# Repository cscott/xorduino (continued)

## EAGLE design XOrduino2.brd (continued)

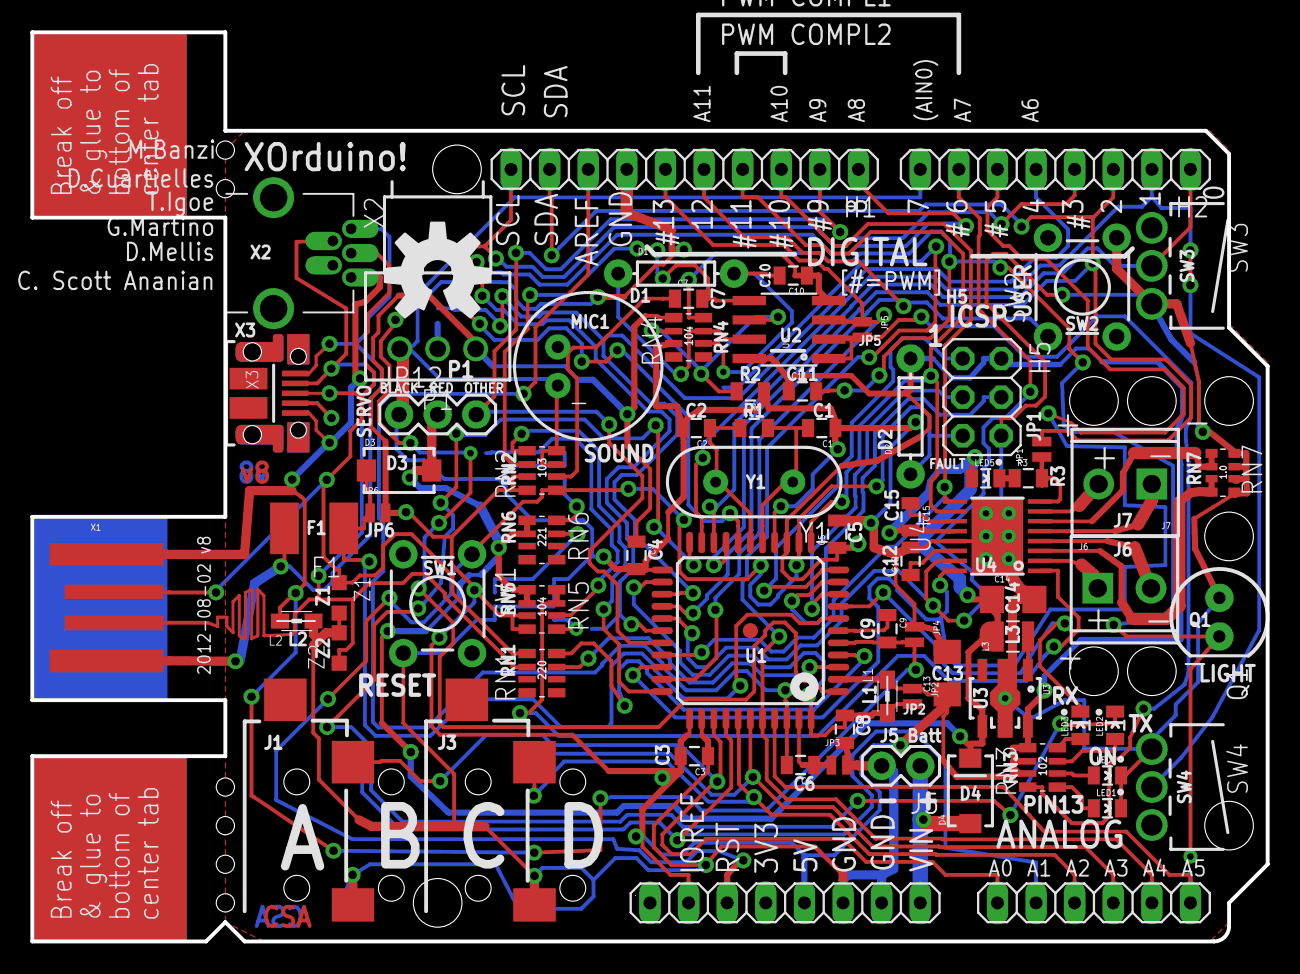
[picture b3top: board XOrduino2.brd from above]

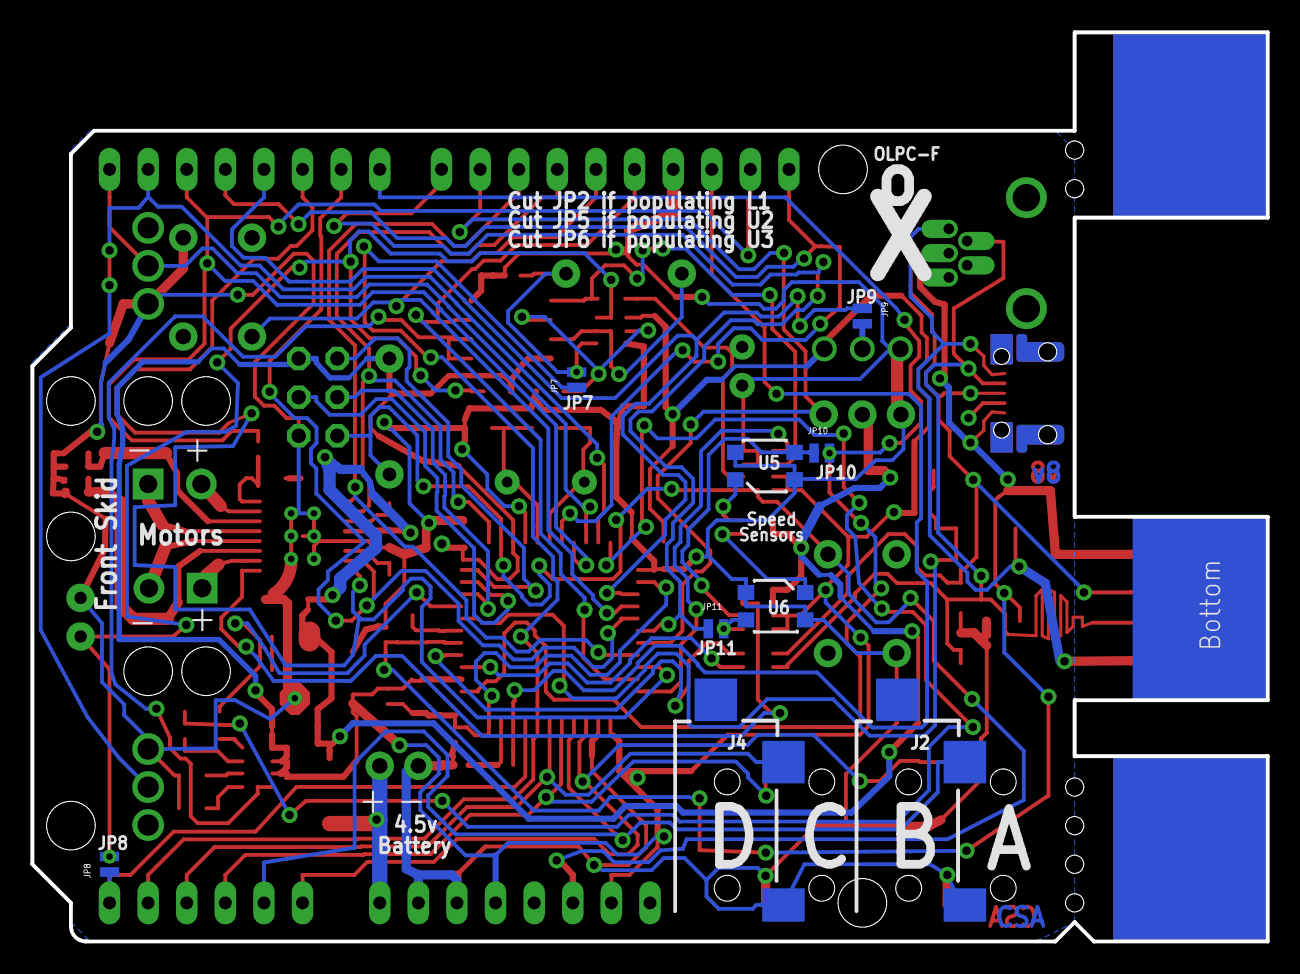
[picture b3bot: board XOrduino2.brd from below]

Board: 4 copper layers, 81.3 x 59.8 mm, 82 parts (4 on the bottom side), 72 nets.

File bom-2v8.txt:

Here's my suggested XO Stick and XOrduino BOMs, with just the bits
really necessary (not all the extras).

The XOrduino BOM was put together with Mitch Bradley's help.  Thanks!

Here is the XOrduino DigiKey BOM organized by sections.  You can paste
individual sections directly into the "Create New BOM (Text File
Import)" dialog.

-- Basic
2,311-1102-1-ND,C1 C2 - 18pF 0805
4,311-1361-1-ND,C2 C3 C4 C5 C6 - 100nF 0805
1,ATMEGA32U4-AU-ND,U1 - ATMEGA32U4-AU
1,445-1589-1-ND,C9 - 1uF
1,587-1356-1-ND,C13 22uF 1206
1,507-1363-1-ND,F1 - 6V 1.1A 1812 PTC Resettable Fuse
1,754-1135-1-ND,LED1 - LED yellow 0805
2,475-1415-1-ND,LED2 LED3 - LED red 0805
1,475-1410-1-ND,LED4 - LED green 0805
10,CRA6S822CT-ND,RN1 - 4x22R (1 required, minimum order is 10)
10,CRA6S810KCT-ND,RN2 - 4x10K (1 required, minimum order is 10)
10,CRA6S81.0KCT-ND,RN3 - 4x1K (1 required, minimum order is 10)
1,450-1652-ND,SW1 - tactile switch
1,CTX1085-ND,Y1 - 16MHz 18pF crystal
1,609-3550-ND,H1 - 10-pin female
2,609-3559-ND,H2 H3 - 8-pin female
1,609-3558-ND,H4 - 6-pin female
1,609-3218-ND,H5 - 3-pin 2-row header

-- Optional
1,311-1.0MARCT-ND,R1 - 1M 0805
1,1N4148FS-ND,D1 - 1N4148
1,445-1589-1-ND,C8 - 1uF 0805
2,L1 L2 - ferrite bead 30 ohm
1,WM17115-ND,X2 - USB mini-B connector
1,609-4050-1-ND,X3 - USB micro-B connector
2,CG0603MLC-05E-ND,Z1 Z2 - ESD suppressor

-- Power Supply
2,641-1014-1-ND,D3 D4 - 1A Schottky SMA
1,587-2055-1-ND,L3 - 100uH 1007
1,587-1356-1-ND,C14 - 22u 1206
1,BC3AAW-ND,J5 - battery holder
1,NJU7261U30-TE1CT-ND,U3 boost regulator XXX I think this is the wrong
one - want 5V out!

-- Scratch Sensor
1,311-1361-1-ND,C7 - 100nF 0805 20%
1,587-1306-1-ND,C10 - .22uF 0805
1,445-1356-1-ND,C11 - .33uF 0805
1,1N4148FS-ND,D2 - 1N4148
1,102-1721-ND,MIC1 - 9.7mm microphone
1,987-1279-ND,P1 - 9mm Pot
1,1080-1019-ND,Q1 - ambient light sensor
1,311-2.2KARCT-ND,R2 - 2.2K 0805
10,CRA6S8100KCT-ND,RN4 - 4x100K (1 required, minimum order is 10)
1,450-1652-ND,SW2 - tactile switch
1,296-9571-1-ND,U2 - LMV358 SOIC-8
4,CP-3523MJCT-ND,J1 J2 J3 J4 3.5mm audio jacks

-- Robot
1,445-1371-1-ND,C12 - 10uF 0805
1,GRM216R71H103KA01D,C15 - .01u 0805 X7R
1,S1012EC-40-ND,JP12 - 3-pin 1-row header
1,475-1415-1-ND,LED5 - LED red 0805
1,A106056CT-ND,R3 - 1K
10,CRA6S8100KCT-ND,RN5 - 4x100K (1 required, minimum order is 10)
10,CRA6S8220CT-ND,RN6 - 4x220R (1 required, minimum order is 10)
1,296-29434-1-ND,U4 - DRV8833PWP motor driver
2,QRE1113GRCT-ND,U5 U6 - light sensor
2,A98036-ND,J6 J7 screw terminal blocks
1,Y91R0CT-ND,RN7 4x1R
1,EG4935-ND,SW3 right snap switch
1,EG4936-ND,SW4 left snap switch

-- Mechanical
1,24438K-ND,Front Skid
2,H744-ND,Front Skid Screw (minimum 100)

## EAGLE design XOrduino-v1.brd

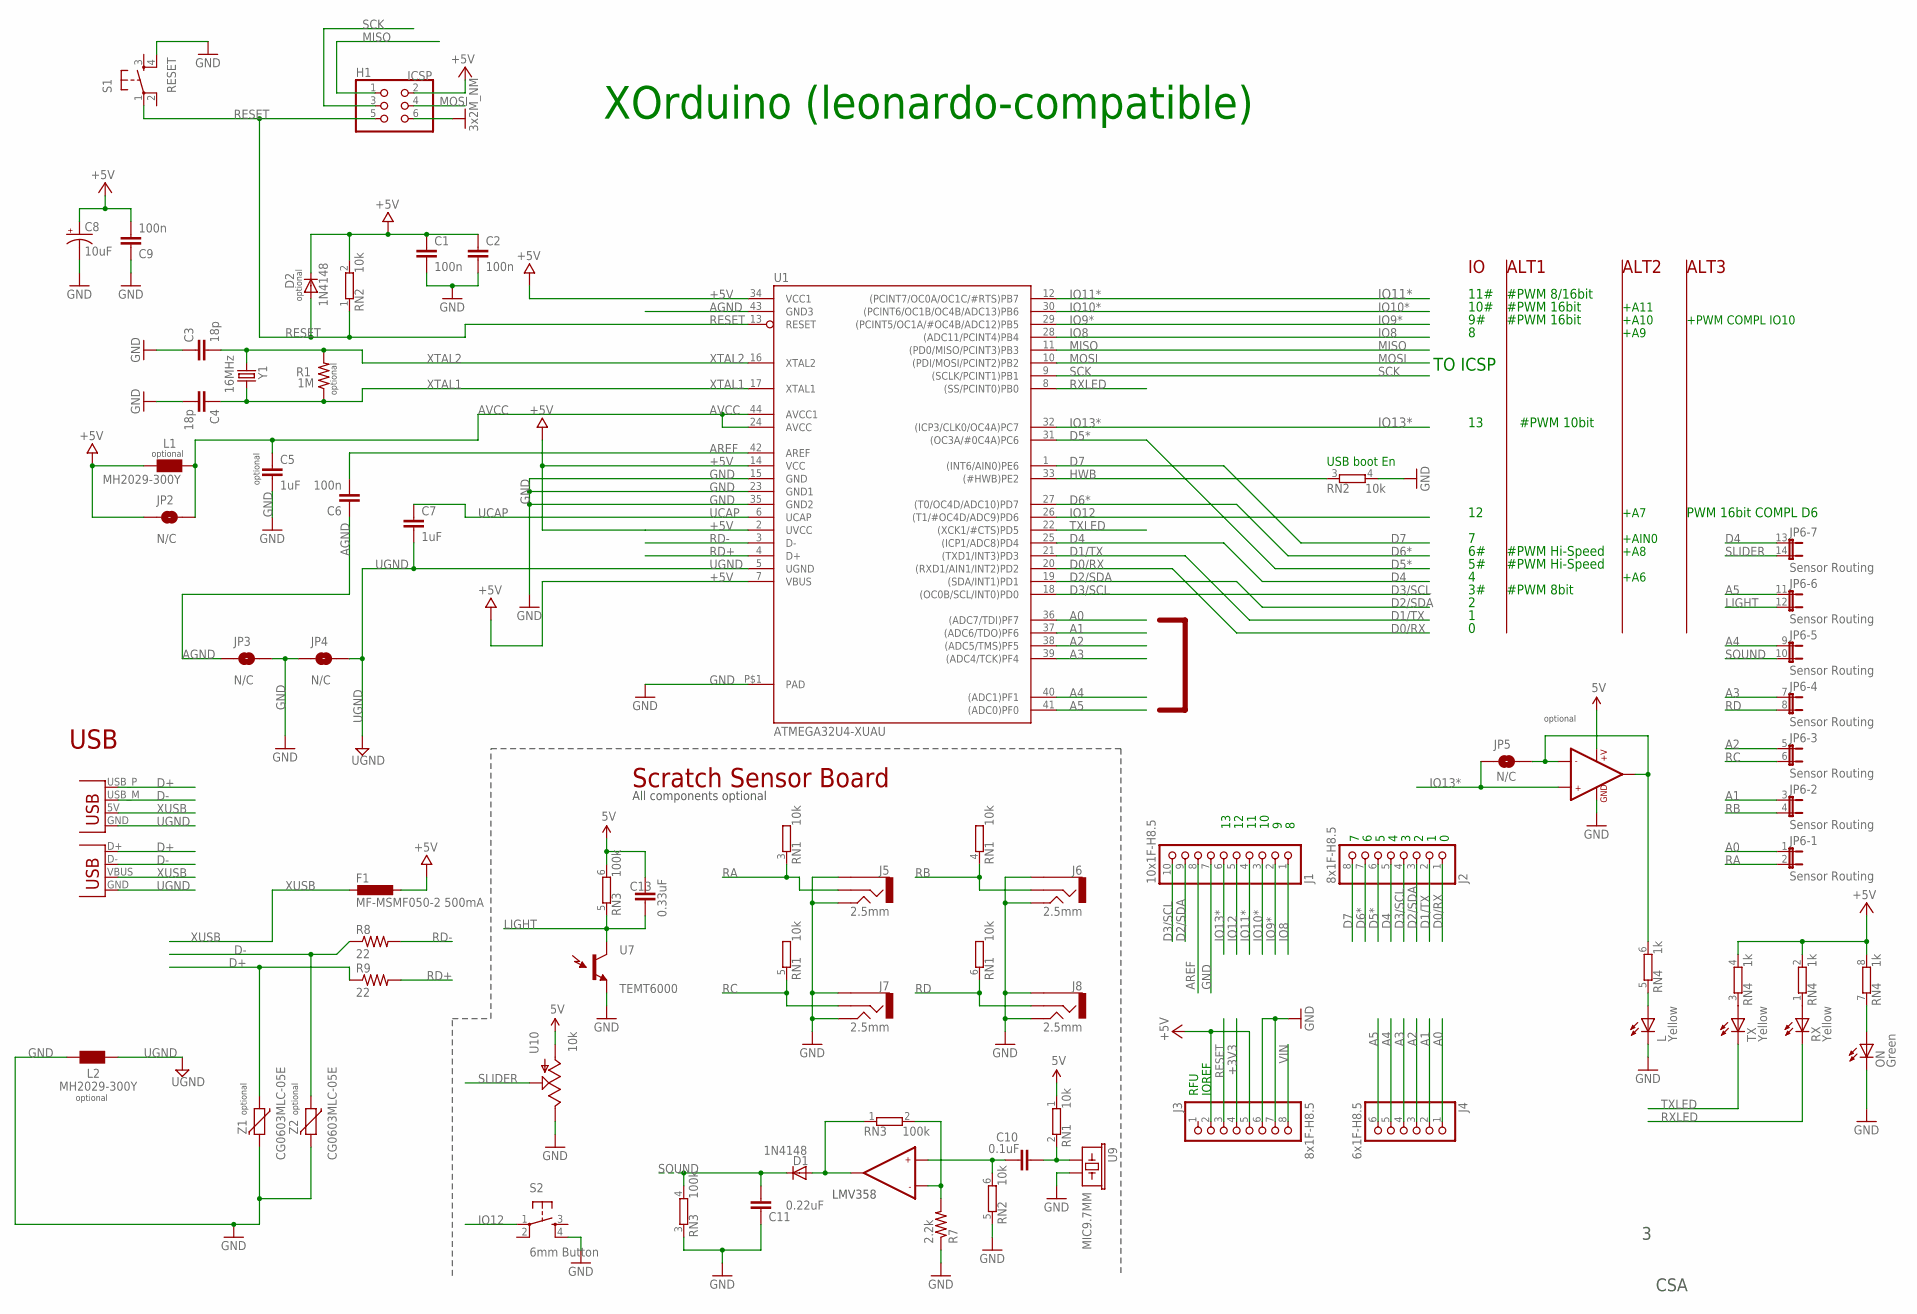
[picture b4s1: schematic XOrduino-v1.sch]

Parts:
C1, C2, C6, C9: 100n; CAP-PTH-SMALL
C3, C4: 18p; CAP-PTH-SMALL
C5, C7: 1uF; CAP-PTH-SMALL
C8: 10uF; CPOL-RADIAL-10UF-25V
C10: 0.1uF; CAP-PTH-SMALL
C11: 0.22uF; CAP-PTH-SMALL
C13: 0.33uF; CAP-PTH-SMALL
D1, D2: 1N4148; DIODE-1N4148
F1: MF-MSMF050-2 500mA; L1812
H1: ICSP; 2X03
J1: 10x1F-H8.5; 1X10
J2, J3: 8x1F-H8.5; 1X08
J4: 6x1F-H8.5; 1X06
J5, J6, J7, J8: 2.5mm; STEREOJACK2.5MM_SMD
JP2, JP3, JP4, JP5: N/C; SJ_2S-TRACE
JP6: Sensor Routing; JP7Q
L: Yellow; LED3MM
L1, L2: MH2029-300Y; 0805
ON: Green; LED3MM
R1: 1M; AXIAL-0.3
R7: 2.2k; AXIAL-0.3
R8, R9: 22; AXIAL-0.3
RN1, RN2: 10k; SIL6
RN3: 100k; SIL6
RN4: 1k; SIL8
RX: Yellow; LED3MM
S1: RESET; TACTILE-PTH
S2: 6mm Button; TACTILE-PTH
TX: Yellow; LED3MM
U1: ATMEGA32U4-XUAU; TQFP44-PAD
U7: TEMT6000; TEMT6000-SEN
U8: LMV358; SO08
U9: MIC9.7MM; MIC-9.7MM
U10: 10k; ALPS_POT
X1: USBPCB; USB-A-PCB
X2: USB-MB-H
Y1: 16MHz; HC49US
Z1, Z2: CG0603MLC-05E; CT/CN0603

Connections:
5V: C13.1, RN1.1, RN3.6 (2), U8.8 (+V), U10.P$3 (A)
+3V3: J3.4
+5V: C1.1, C2.1, C8.1 (+), C9.2, D2.C, F1.1, H1.2, J3.2, J3.5, JP2.1, L1.1, RN2.2, RN4.2, RN4.4 (2), RN4.8 (2), U1.2 (UVCC), U1.7 (VBUS), U1.14 (VCC), U1.34 (VCC1)
A0: J4.1, JP6.1, U1.36 ((ADC7/TDI)PF7)
A1: J4.2, JP6.3 (1), U1.37 ((ADC6/TDO)PF6)
A2: J4.3, JP6.5 (1), U1.38 ((ADC5/TMS)PF5)
A3: J4.4, JP6.7 (1), U1.39 ((ADC4/TCK)PF4)
A4: J4.5, JP6.9 (1), U1.40 ((ADC1)PF1)
A5: J4.6, JP6.11 (1), U1.41 ((ADC0)PF0)
AGND: C6.1, JP3.1, U1.43 (GND3)
AREF: C6.2, J1.8, U1.42 (AREF)
AVCC: C5.1, JP2.2, L1.2, U1.24 (AVCC), U1.44 (AVCC1)
D0/RX: J2.1, U1.20 ((RXD1/AIN1/INT2)PD2)
D1/TX: J2.2, U1.21 ((TXD1/INT3)PD3)
D2/SDA: J1.9, J2.3, U1.19 ((SDA/INT1)PD1)
D3/SCL: J1.10, J2.4, U1.18 ((OC0B/SCL/INT0)PD0)
D4: J2.5, JP6.13 (1), U1.25 ((ICP1/ADC8)PD4)
D5*: J2.6, U1.31 ((OC3A/#0C4A)PC6)
D6*: J2.7, U1.27 ((T0/OC4D/ADC10)PD7)
D7: J2.8, U1.1 ((INT6/AIN0)PE6)
D+: R9.P$1 (1), X1.USB_P (D+), X2.D+, Z1.1
D-: R8.P$1 (1), X1.USB_M (D-), X2.D-, Z2.1
GND: C1.2, C2.2, C3.1, C4.2, C5.2, C8.2 (-), C9.1, C11.1, H1.6, J1.7, J3.6, J3.7, J5.1 (5), J5.5 (1), J6.1 (5), J6.5 (1), J7.1 (5), J7.5 (1), J8.1 (5), J8.5 (1), JP3.2, JP4.1, L.K (C), L2.2, ON.K (C), R7.P$1 (1), RN2.4 (2), RN2.5 (1), RN3.3 (1), S1.4, S2.4, U1.15 (GND), U1.23 (GND1), U1.35 (GND2), U1.P$1 (PAD), U7.EMITTER (E1), U8.4 (GND), U9.2, U10.P$1 (E), Z1.2, Z2.2
HWB: RN2.3 (1), U1.33 ((#HWB)PE2)
IO8: J1.1, U1.28 ((ADC11/PCINT4)PB4)
IO9*: J1.2, U1.29 ((PCINT5/OC1A/#OC4B/ADC12)PB5)
IO10*: J1.3, U1.30 ((PCINT6/OC1B/OC4B/ADC13)PB6)
IO11*: J1.4, U1.12 ((PCINT7/OC0A/OC1C/#RTS)PB7)
IO12: J1.5, S2.1, U1.26 ((T1/#OC4D/ADC9)PD6)
IO13*: J1.6, JP5.1, U1.32 ((ICP3/CLK0/OC4A)PC7), U8.3 (+IN1)
LIGHT: C13.2, JP6.12 (2), RN3.5 (1), U7.COLLECTOR (C1)
MISO: H1.1, U1.11 ((PD0/MISO/PCINT3)PB3)
MOSI: H1.4, U1.10 ((PDI/MOSI/PCINT2)PB2)
unnamed: RN4.3 (1), TX.A
unnamed: L.A, RN4.5 (1)
unnamed: ON.A, RN4.7 (1)
unnamed: RN4.1, RX.A
unnamed: R7.P$2 (2), RN3.2, U8.6 (-IN2)
unnamed: JP5.2, RN4.6 (2), U8.1 (OUT1), U8.2 (-IN1)
unnamed: C10.1, RN1.2, U9.1
unnamed: C10.2, RN2.6 (2), U8.5 (+IN2)
unnamed: D1.A, RN3.1, U8.7 (OUT2)
RA: J5.4 (2), JP6.2, RN1.3 (2)
RB: J6.4 (2), JP6.4 (2), RN1.4 (2)
RC: J7.4 (2), JP6.6 (2), RN1.5 (2)
RD: J8.4 (2), JP6.8 (2), RN1.6 (2)
RD+: R9.P$2 (2), U1.4 (D+)
RD-: R8.P$2 (2), U1.3 (D-)
RESET: D2.A, H1.5, J3.3, RN2.1, S1.1, U1.13 (RESET)
RXLED: RX.K (C), U1.8 ((SS/PCINT0)PB0)
SCK: H1.3, U1.9 ((SCLK/PCINT1)PB1)
SLIDER: JP6.14 (2), U10.P$2 (S)
SOUND: C11.2, D1.C, JP6.10 (2), RN3.4 (2)
TXLED: TX.K (C), U1.22 ((XCK1/#CTS)PD5)
UCAP: C7.1, U1.6 (UCAP)
UGND: C7.2, JP4.2, L2.1, U1.5 (UGND), X1.GND, X2.GND
VIN: J3.8
XTAL1: C4.1, R1.P$1 (1), U1.17 (XTAL1), Y1.2
XTAL2: C3.2, R1.P$2 (2), U1.16 (XTAL2), Y1.1
XUSB: F1.2, X1.5V (VBUS), X2.VBUS

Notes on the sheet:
XOrduino (leonardo-compatible)
USB boot En
USB
TO ICSP
10#
11#
#PWM 8bit
#PWM Hi-Speed
#PWM 8/16bit
#PWM 16bit
PWM 16bit COMPL D6
#PWM 10bit
+A6
+A7
IOREF
RFU
+A11
+A10
+A8
+A9
+PWM COMPL IO10
+AIN0
ALT1
ALT2
ALT3
optional
CSA
Scratch Sensor Board
LMV358
All components optional

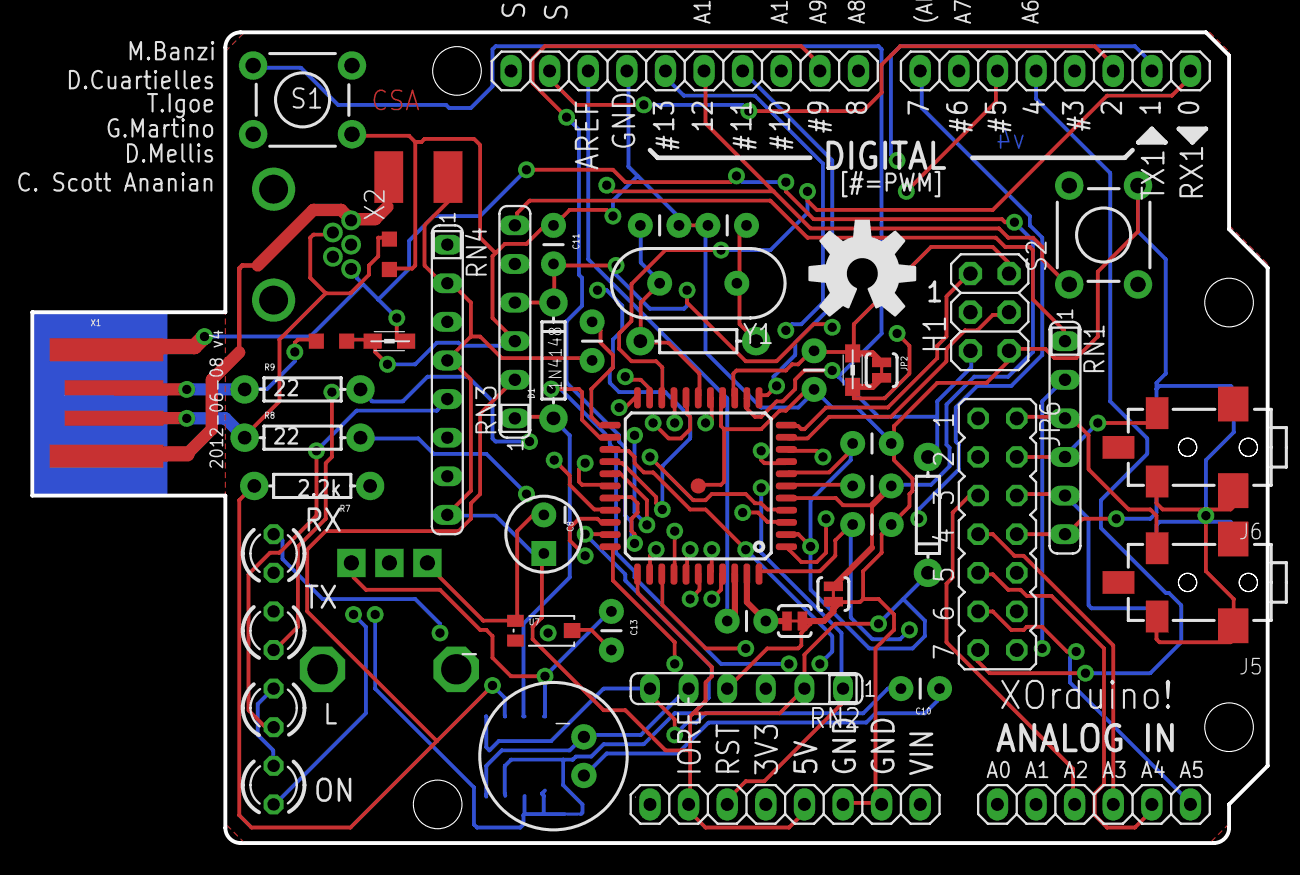
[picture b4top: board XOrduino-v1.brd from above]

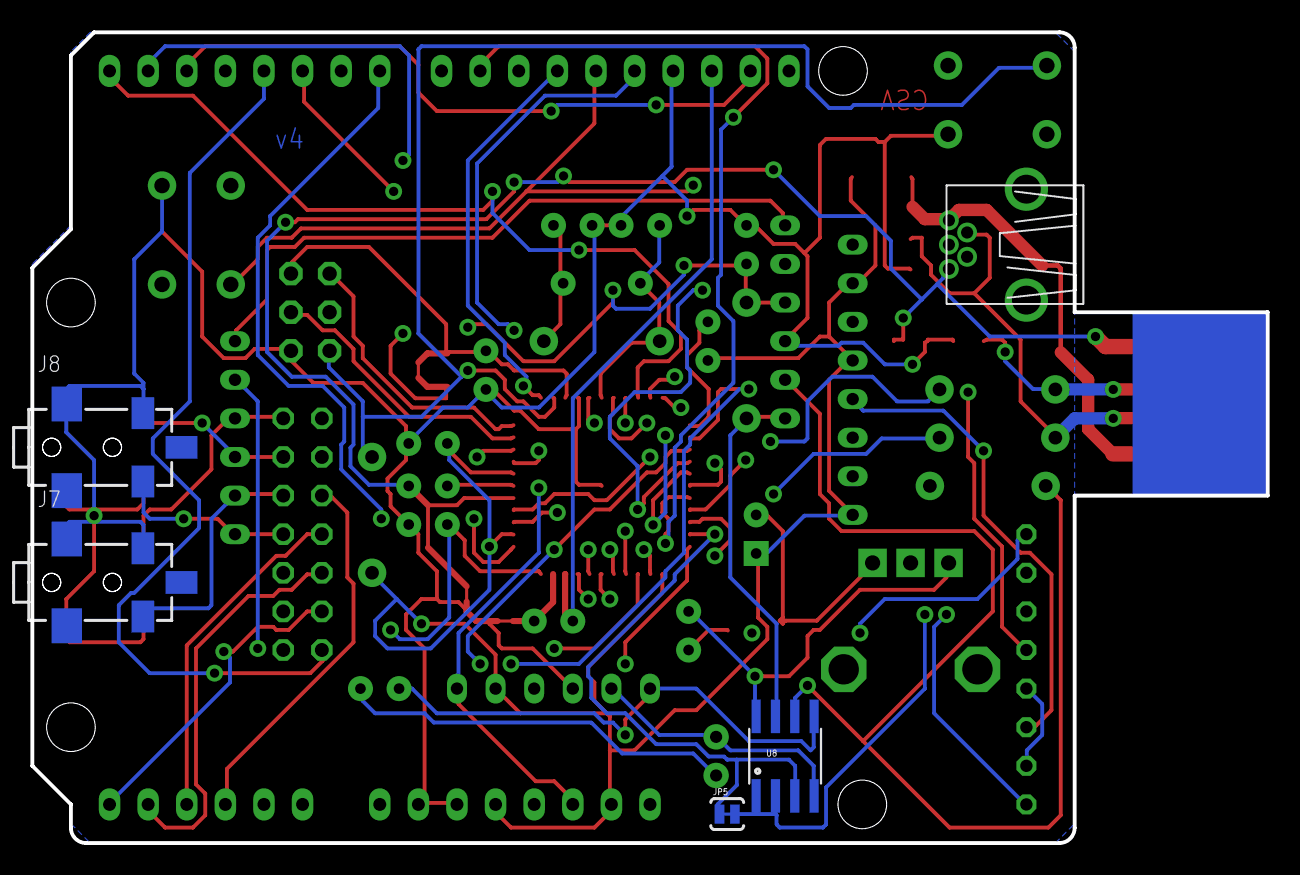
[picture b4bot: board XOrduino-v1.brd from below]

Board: 4 copper layers, 81.3 x 53.3 mm, 56 parts (4 on the bottom side), 58 nets.

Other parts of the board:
U$5: OSHW-LOGOL; OSHW-LOGO-L

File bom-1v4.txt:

Partlist (v4)

alternative to 478-5741-ND: 478-3192-ND ($0.11)
xx: look at using the RC suffixed version of the ATMEGA32U4, avoids need for crystal
ie, ATMEGA32U4RC-AU-ND (low speed USB only)
alternative to 4608X-2-102LF-ND: 987-1254-ND
rename C13 to C12
U7's price is ridiculous
rename R7/R8/R9 to R4/R2/R3

REQUIRED:
Part     Value              Device            Package              Library                    Digikey   Cost (qty 100)
C1       100n               CAPPTH            CAP-PTH-SMALL        SparkFun-Passives          478-5741-ND           $0.09450 (.100" lead spacing)
C2       100n               CAPPTH            CAP-PTH-SMALL        SparkFun-Passives          478-5741-ND           $0.09450 (.100" lead spacing)
C3       18p                CAPPTH            CAP-PTH-SMALL        SparkFun-Passives          BC1004CT-ND           $0.11760 (.100" lead spacing)
C4       18p                CAPPTH            CAP-PTH-SMALL        SparkFun-Passives          BC1004CT-ND           $0.11760 (.100" lead spacing)
C6       100n               CAPPTH            CAP-PTH-SMALL        SparkFun-Passives          478-5741-ND           $0.09450 (.100" lead spacing)
C7       1uF                CAPPTH            CAP-PTH-SMALL        SparkFun-Passives          P5174-ND              $0.06800  (.08" lead spacing)
C8       10uF               CAP_POLPTH2       CPOL-RADIAL-10UF-25V SparkFun-Passives          399-6100-ND           $0.05350  (.08" lead spacing)
C9       100n               CAPPTH            CAP-PTH-SMALL        SparkFun-Passives          478-5741-ND           $0.09450 (.100" lead spacing)
F1       MF-MSMF050-2 500mA L-EUL1812         L1812                rcl                        MF-MSMF050-2CT-ND $0.1475 500mA 15V fuse 1812 footprint 
L        Yellow             LED3MM            LED3MM               led                        754-1212-ND       $0.08250 3mm T1 yellow
RX       Yellow             LED3MM            LED3MM               led                        754-1218-ND       $0.07150 3mm T1 red
TX       Yellow             LED3MM            LED3MM               led                        754-1218-ND       $0.07150 3mm T1 red
ON       Green              LED3MM            LED3MM               led                        754-1217-ND       $0.07150 3mm T1 green
R8       22                 RESISTORAXIAL-0.3 AXIAL-0.3            SparkFun-Passives          CF14JT22R0CT-ND   $0.02190
R9       22                 RESISTORAXIAL-0.3 AXIAL-0.3            SparkFun-Passives          CF14JT22R0CT-ND   $0.02190
RN2      10k                E3RP              SIL6                 resistor-sil               4606X-2-103LF-ND  $0.08440 3x10k isolated, 6-SIP 
RN4      1k                 E4RP              SIL8                 resistor-sil               4608X-2-102LF-ND  $0.11320  4x1k isolated, 8-SIP 
S1       RESET 6mm          TAC_SWITCHPTH     TACTILE-PTH          SparkFun-Electromechanical 450-1652-ND       $0.1114
U1       ATMEGA32U4-XUAU    ATMEGA32U4-XUAU   TQFP44-PAD           SmartPrj                   ATMEGA32U4-AU-ND  $3.36840
Y1       16MHz HC49,18pF    CRYSTALHC49US     HC49US               SparkFun-FreqCtrl          CTX1085-ND        $0.2320

OPTIONAL:
Part     Value              Device            Package              Library                    Sheet

C5       1uF                CAPPTH            CAP-PTH-SMALL        SparkFun-Passives          P5174-ND              $0.06800  (.08" lead spacing)
C10      0.1uF              CAPPTH            CAP-PTH-SMALL        SparkFun-Passives          478-5741-ND           $0.09450 (.100" lead spacing)
C11      0.22uF             CAPPTH            CAP-PTH-SMALL        SparkFun-Passives          P821-ND               $0.08020  (.06"/1.5mm)
C13      0.33uF             CAPPTH            CAP-PTH-SMALL        SparkFun-Passives          P822-ND               $0.08020  (.06"/1.5mm)
D1       1N4148             DIODE1N4148       DIODE-1N4148         SparkFun-DiscreteSemi      1N4148FS-ND           $0.03690 (DO-35)
D2       1N4148             DIODE1N4148       DIODE-1N4148         SparkFun-DiscreteSemi      1N4148FS-ND           $0.03690 (DO-35)
H1       ICSP               PINHD-2X3         2X03                 SmartPrj                   609-3218-ND           $0.1778
J1       10x1F-H8.5         PINHD-1X10        1X10                 SmartPrj                   1
J2       8x1F-H8.5          PINHD-1X8         1X08                 SmartPrj                   1
J3       8x1F-H8.5          PINHD-1X8         1X08                 SmartPrj                   1
J4       6x1F-H8.5          PINHD-1X6         1X06                 SmartPrj                   1
                                                                                              S1012EC-40-ND         0.37800 (1x40, for J1/J2/J3/J4)
J5       2.5mm              AUDIO-JACKSMD     STEREOJACK2.5MM_SMD  SparkFun                   CP-2523MJCT-ND
J6       2.5mm              AUDIO-JACKSMD     STEREOJACK2.5MM_SMD  SparkFun                   CP-2523MJCT-ND
J7       2.5mm              AUDIO-JACKSMD     STEREOJACK2.5MM_SMD  SparkFun                   CP-2523MJCT-ND
J8       2.5mm              AUDIO-JACKSMD     STEREOJACK2.5MM_SMD  SparkFun                   CP-2523MJCT-ND
L1       MH2029-300Y        WE-CBF_0805       0805                 wuerth-elektronik          MH2029-300Y-ND    $0.0174 300 ohm bead ferrite (qty 4000)
L2       MH2029-300Y        WE-CBF_0805       0805                 wuerth-elektronik          MH2029-300Y-ND    $0.0174 300 ohm bead ferrite (qty 4000)
R1       1M                 RESISTORAXIAL-0.3 AXIAL-0.3            SparkFun-Passives          S1MQCT-ND         $0.02280
R7       2.2k               RESISTORAXIAL-0.3 AXIAL-0.3            SparkFun-Passives          CF14JT2K20CT-ND   $0.02190
RN1      10k                GE05RP            SIL6                 resistor-sil               4606X-1-103LF-ND  $0.08440 5x10k bussed, 6-SIP
RN3      100k               E3RP              SIL6                 resistor-sil               4606X-2-104LF-ND  $0.08440 3x100k isolated, 6-SIP
S2       6mm Button         TAC_SWITCHPTH     TACTILE-PTH          SparkFun-Electromechanical 450-1652-ND       $0.1114  6mm
U7       TEMT6000           TEMT6000          TEMT6000-SEN         SparkFun                   751-1055-1-ND     $0.90450
U8       LMV358IDR          LMV358            SO08                 SparkFun                   296-9571-1-ND     $0.15 8-SOIC
U9       MIC9.7MM           MIC9.7MM          MIC-9.7MM            SparkFun                   102-1721-ND       $0.56930
U10      10k                POT               ALPS_POT             SparkFun-Electromechanical 987-1276-ND       $0.46
X2       USB                USB               USB-MB-H2            xorduino                   WM17115-ND        $1.1038 USB mini-B through hole
Z1       CG0603MLC-05E      VARISTORCN0603    CT/CN0603            varistor                   CG0603MLC-05E-ND  $0.06916 5VDC 0603 ESD suppressor (qty 10,000)
Z2       CG0603MLC-05E      VARISTORCN0603    CT/CN0603            varistor                   CG0603MLC-05E-ND  $0.06916 5VDC 0603 ESD suppressor (qty 10,000)

OTHER:
JP2      N/C                SOLDERJUMPERTRACE SJ_2S-TRACE          SparkFun-Passives          1
JP3      N/C                SOLDERJUMPERTRACE SJ_2S-TRACE          SparkFun-Passives          1
JP4      N/C                SOLDERJUMPERTRACE SJ_2S-TRACE          SparkFun-Passives          1
JP5      N/C                SOLDERJUMPERTRACE SJ_2S-TRACE          SparkFun-Passives          1
JP6      Sensor Routing     JP7QES            JP7QS                xorduino                   1
X1       USBPCB             USBPCB            USB-A-PCB            SparkFun-Connectors        1

=========


RN4 alternate is: 987-1254-ND      $0.11390
C3/C4 alternate is 1428PH-ND             $0.11730 (.250" lead spacing)

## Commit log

2012-06-05 Initial checkin of inspirational designs.
2012-06-07 First draft of XOrduino schematic.
2012-06-07 Color version of XOrdiuno schematic.
2012-06-07 Attempt to route the board. 90% routed; may need to go to 4 layer board.
2012-06-07 First full layout for XOrduino. (v1)
2012-06-07 XOrduino v2 -- move USB plug up a bit to allow XOstick to fit underneath.
2012-06-07 Version 3: silkscreen improvements (no silkscreen off board)
2012-06-07 Rename gerber zip so there's no confusion about what version it is.
2012-06-08 XOrduino v4. Updated silkscreen, shorting jumpers for sensor lines; tweak USB-B.
2012-06-09 Rename XOrduino-v1 to XOrduino to avoid confusion.
2012-06-09 Update BOM for v4; classify components, add some pricing information.
2012-06-09 README describing design choices, tradeoffs, etc.
2012-06-10 Update BOM (fill in more digikey part numbers and prices).
2012-06-20 Include solder paste layers in the gerber .zip, just in case that's useful.
2012-07-15 Update BOM, notes on v4 design based on 1st assembly of boards from OEM.
2012-07-18 More notes on v4 design.
2012-07-18 Updated BOM for XOrduino and XOstick (A1 version).
2012-07-18 First commit of 'XOrdiuno2' redesign (turtle robot capable).
    Main changes in XOrduino2: integration of motor driver, bump switches,
    optical sensor, and battery/external power supply. In addition, various
    fixes found necessary on XOrduino v4 boards (ie with Scratch Sensor Board
    functionality). I'm also investigating a broader switch to SMT devices,
    for cost and space reasons. The XO Stick will remain a through-hole
    design; XOrduino may become an 'easy' SMT kit.
2012-07-24 First version of Xorduino2 (v5) board w/ all components placed.
2012-07-24 70% 2-layer routed version of XOrduino2.
2012-07-25 Almost-completely 4-layer routed version of XOrduino2.
2012-07-25 97% routed 4-layer XOrduino.
2012-07-25 First fully-routed version of XOrduino2 (4-layer).
2012-07-26 Tweaks for better 2-layer routability.
2012-07-26 Best 2-layer XOrduino layout generated by Eagle.
    1mil grid, diagonal route direction preference, 95% routed.
2012-07-27 Fully-routed 2-layer version of XOrduino. Thanks to freerouting.net.
2012-07-28 v5 gerbers.
2012-07-29 Attempt 2 at routing the XOrduino2 board, via 10mil traces & spaces this time.
    ...however, the router still doesn't have quite the right via clearances.
2012-07-30 Xorduino v6: rerouting with bigger vias, 10 mil traces, and better spacing.
    Also added silkscreen, etc. and regenerated PDFs.
2012-07-30 Clean up old A1 files to avoid confusion.
2012-07-30 Update README for v6.
2012-08-03 v7: Update USB mini-B footprint & bom; more heat sink area for motor driver.
    Went through and widened power traces as much as I could, as well.
2012-08-03 Minor silkscreen tweaks, extend L3 pads a hair.
2012-08-03 XOrduino2 v8. Rename nets for better manual auditing, silkscreen tweaks.
2012-08-03 Update schematic and board PDFs.
2012-08-06 Programmer with ZIF socket for the ATmega32U4.
2012-08-08 Tweak README formatting.
2012-08-10 Add drill table layer; regenerate Gerbers in vendor-approved format.
    The drill table was made with drillegend-stack.ulp. It has a problem deleting
    an existing drill table (see
    http://www.eaglecentral.ca/forums/index.php/mv/msg/46577/145423/
    ) so I've saved the .brd file with the drill legend as XOrduino2-drilltable.brd.
    If changes are necessary to XOrduino2.brd, regenerate XOrduino2-drilltable.brd
    from XOrduino2.brd after making the changes.
2012-08-13 Hall Effect Sensor Test Shield, v1.
2013-06-24 Chack in updated BOM for XOrduino2 v8 boards.
2013-06-24 Small updates to BOM.
